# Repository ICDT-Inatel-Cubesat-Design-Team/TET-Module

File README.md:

<div align="center">
  
</div>
<h1 align="center">TET Module</h1>

<p align="center">

</p>

<p align="center">
    <a href="#overview">Overview</a> •
    <a href="#repository-organization">Repository Organization</a> •
    <a href="#releases">Releases</a> •
    <a href="#references">References</a> •
    <a href="#license">License</a>
</p>

## Overview
This project involves the development of the **TET (Telemetry, Encoding & Transmission)** module tailored for a 1U CubeSat platform. The system is engineered to handle TT&C (Tracking, Telemetry, and Command) capabilities, providing long-range telemetry and low-power wireless communication based on the Semtech LR1121 RF transceiver architecture and an STM32L431 microcontroller.

**Technical Parameters**
- **RF Architecture:** E80-900M2213S (LR1121)
- **Supported Bands:** Dual-band operation (915 MHz and 2.4 GHz)
- **Modulation Schemes:** LoRa, GFSK, FLRC, and LR-FHSS.
- **RF Interfaces:** Dedicated SMA/IPEX outputs for external antennas
- **External Interfaces:** SPI, GPIO, and CAN bus (via TCAN3414).
- **Power Input:** 3 independent 5 V input channels from the EPS (via PC/104)
- **Power Regulation:** Independent, regulated low-noise 3.3 V rail.
- **Onboard Sensors:** INA226 (current and voltage monitoring) and TMP112 (temperature monitoring and thermal alerts via I2C).
- **Storage:** 3 external SPI flash memories configured with TMR (Triple Modular Redundancy) for telemetry buffering and data storage.

## Repository Organization

* `docs`: Technical documentation and datasheets.
* `hardware`: Core hardware files.
    * `3D`: 3D models (.step).
    * `Fabrication`: BOM and Gerber files for JLCPCB manufacturing.
    * `PCB`: KiCad schematics and layout design.
* `firmware`: Examples of firmware implementation.

## Releases

<table>
  <thead>
    <tr>
      <th>Render</th>
      <th>Board Name</th>
      <th>Status</th>
      <th>Latest Release</th>
      <th>Date</th>
      <th>Datasheet</th>
      <th>BOM</th>
      <th>Ordering Info</th>
    </tr>
  </thead>
  <tbody>
    <tr>
      <td></td>
      <td>TET Module v1</td>
      <td>🧪 Testing</td>
      <td><a href="https://github.com/ICDT-Inatel-Cubesat-Design-Team/TET-Module/releases/tag/v1r2">v1r2</a></td>
      <td>09-06-2026</td>
      <td></td>
      <td>Yes</td>
      <td><a href="hardware/Fabrication/GERBER-TET.zip">GERBER</a> (JLCPCB)</td>
    </tr>
  </tbody>
</table>

## References

This project was inspired by the [TTC](https://github.com/spacelab-ufsc/ttc) and [TTC2](https://github.com/spacelab-ufsc/ttc2) modules from [SpaceLab](https://github.com/spacelab-ufsc/spacelab) UFSC, and the [Build a CubeSat](https://buildacubesat.space/) project. Thank you to both for making your work open-source, and a special thanks to the Build a CubeSat community for their support.

**Missions Associated with this Project**

<p>

<p>

## License

This project is licensed under the permissive, weakly-reciprocal **[CERN-OHL-W-2.0](LICENSE)** open-hardware license. You are free to modify and distribute these files, provided downstream hardware design modifications remain under the same terms.

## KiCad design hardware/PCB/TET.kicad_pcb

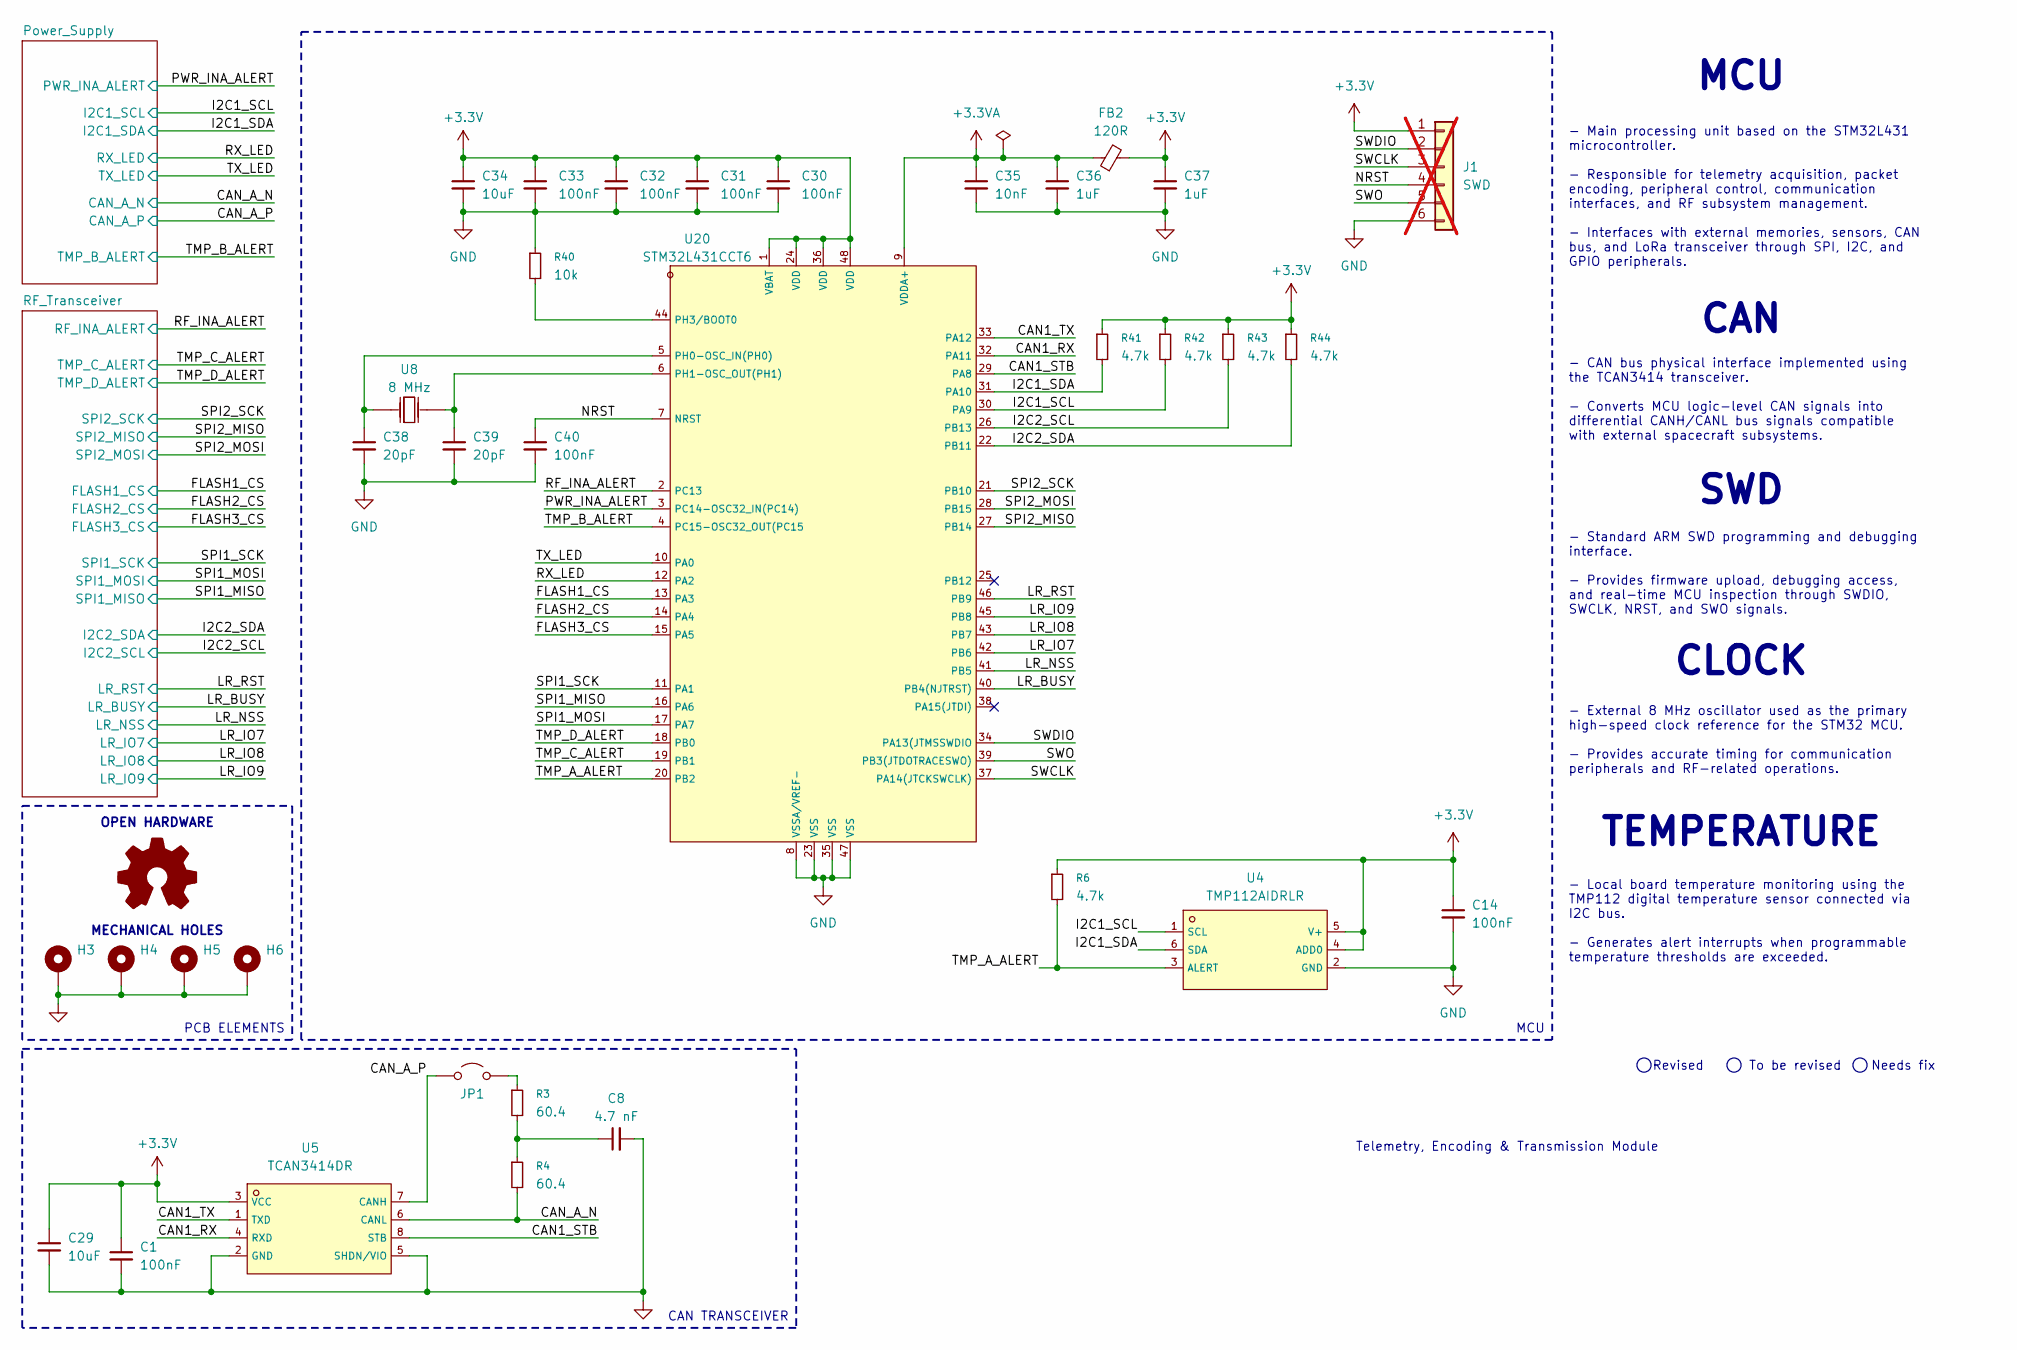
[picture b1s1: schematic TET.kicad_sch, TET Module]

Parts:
C1, C14, C30, C31, C32, C33, C40: 100nF; C_0402_1005Metric
C8: 4.7 nF; C_0402_1005Metric
C29, C34: 10uF; C_0805_2012Metric
C35: 10nF; C_0402_1005Metric
C36, C37: 1uF; C_0402_1005Metric
C38, C39: 20pF; C_0402_1005Metric
FB2: 120R; L_0603_1608Metric; LCSC C14709
H3, H4, H5, H6: MountingHole_Pad; MountingHole_3.2mm_M3_Pad_Via
J1: SWD; PinHeader_1x06_P2.54mm_Vertical; not fitted
JP1: Jumper_2_Open; SolderJumper-2_P1.3mm_Open_TrianglePad1.0x1.5mm
R3, R4: 60.4; R_0402_1005Metric
R6, R41, R42, R43, R44: 4.7k; R_0402_1005Metric
R40: 10k; R_0402_1005Metric
REF1: Logo_Open_Hardware_Small; OSHW-Logo_5.7x6mm_SilkScreen
U4: TMP112AIDRLR; SOT-563_L1.6-W1.2-P0.50-LS1.6-BR; LCSC C28927
U5: TCAN3414DR; SOIC-8_L4.9-W3.9-P1.27-LS6.0-BL; LCSC C22396693
U8: 8 MHz; CRYSTAL-SMD_L5.0-W3.2; LCSC C115962
U20: STM32L431CCT6; LQFP-48_L7.0-W7.0-P0.50-LS9.0-BL; LCSC C486681

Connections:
+3.3V: C1.1, C14.1, C29.1, C30.1, C31.1, C32.1, C33.1, C34.1, C37.1, FB2.2, J1.1, R6.1, R41.1, R42.1, R43.1, R44.1, U4.4 (ADD0), U4.5 (V+), U5.3 (VCC), U20.1 (VBAT), U20.24 (VDD), U20.36 (VDD), U20.48 (VDD); also elsewhere on the board
+3.3VA: C35.1, C36.1, FB2.1, U20.9 (VDDA+)
/CAN1_RX: U5.4 (RXD), U20.32 (PA11)
/CAN1_STB: U5.8 (STB), U20.29 (PA8)
/CAN1_TX: U5.1 (TXD), U20.33 (PA12)
/CAN_A_N: R4.2, U5.6 (CANL); also elsewhere on the board
/CAN_A_P: JP1.1 (A), U5.7 (CANH); also elsewhere on the board
/FLASH1_CS: U20.13 (PA3); also elsewhere on the board
/FLASH2_CS: U20.14 (PA4); also elsewhere on the board
/FLASH3_CS: U20.15 (PA5); also elsewhere on the board
/I2C1_SCL: R42.2, U4.1 (SCL), U20.30 (PA9); also elsewhere on the board
/I2C1_SDA: R41.2, U4.6 (SDA), U20.31 (PA10); also elsewhere on the board
/I2C2_SCL: R43.2, U20.26 (PB13); also elsewhere on the board
/I2C2_SDA: R44.2, U20.22 (PB11); also elsewhere on the board
/LR_BUSY: U20.40 (PB4(NJTRST)); also elsewhere on the board
/LR_IO7: U20.42 (PB6); also elsewhere on the board
/LR_IO8: U20.43 (PB7); also elsewhere on the board
/LR_IO9: U20.45 (PB8); also elsewhere on the board
/LR_NSS: U20.41 (PB5); also elsewhere on the board
/LR_RST: U20.46 (PB9); also elsewhere on the board
/NRST: C40.1, J1.4, U20.7 (NRST)
/PWR_INA_ALERT: U20.3 (PC14-OSC32_IN(PC14)); also elsewhere on the board
/RF_INA_ALERT: U20.2 (PC13); also elsewhere on the board
/RX_LED: U20.12 (PA2); also elsewhere on the board
/SPI1_MISO: U20.16 (PA6); also elsewhere on the board
/SPI1_MOSI: U20.17 (PA7); also elsewhere on the board
/SPI1_SCK: U20.11 (PA1); also elsewhere on the board
/SPI2_MISO: U20.27 (PB14); also elsewhere on the board
/SPI2_MOSI: U20.28 (PB15); also elsewhere on the board
/SPI2_SCK: U20.21 (PB10); also elsewhere on the board
/SWCLK: J1.3, U20.37 (PA14(JTCKSWCLK))
/SWDIO: J1.2, U20.34 (PA13(JTMSSWDIO)
/SWO: J1.5, U20.39 (PB3(JTDOTRACESWO))
/TMP_A_ALERT: R6.2, U4.3 (ALERT), U20.20 (PB2)
/TMP_B_ALERT: U20.4 (PC15-OSC32_OUT(PC15); also elsewhere on the board
/TMP_C_ALERT: U20.19 (PB1); also elsewhere on the board
/TMP_D_ALERT: U20.18 (PB0); also elsewhere on the board
/TX_LED: U20.10 (PA0); also elsewhere on the board
GND: C1.2, C8.2, C14.2, C29.2, C30.2, C31.2, C32.2, C33.2, C34.2, C35.2, C36.2, C37.2, C38.2, C39.2, C40.2, H3.1 (1_1), H4.1 (1_1), H5.1 (1_1), H6.1 (1_1), J1.6, R40.1, U4.2 (GND), U5.2 (GND), U5.5 (SHDN/VIO), U20.8 (VSSA/VREF-), U20.23 (VSS), U20.35 (VSS), U20.47 (VSS); also elsewhere on the board
unnamed: C8.1, R3.2, R4.1
unnamed: JP1.2 (B), R3.1
unnamed: C38.1, U8.2 (OSC2), U20.5 (PH0-OSC_IN(PH0))
unnamed: C39.1, U8.1 (OSC1), U20.6 (PH1-OSC_OUT(PH1))
unnamed: R40.2, U20.44 (PH3/BOOT0)

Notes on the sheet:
SWD
Revised
TEMPERATURE
Needs fix
MCU
OPEN HARDWARE
CLOCK
MECHANICAL HOLES
To be revised
CAN
Telemetry, Encoding & Transmission Module
PCB ELEMENTS
CAN TRANSCEIVER
- Main processing unit based on the STM32L431 microcontroller. - Responsible for telemetry acquisition, packet encoding, peripheral control, communication interfaces, and RF subsystem management. - Interfaces with external memories, sensors, CAN bus, and LoRa transceiver through SPI, I2C, and GPIO 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

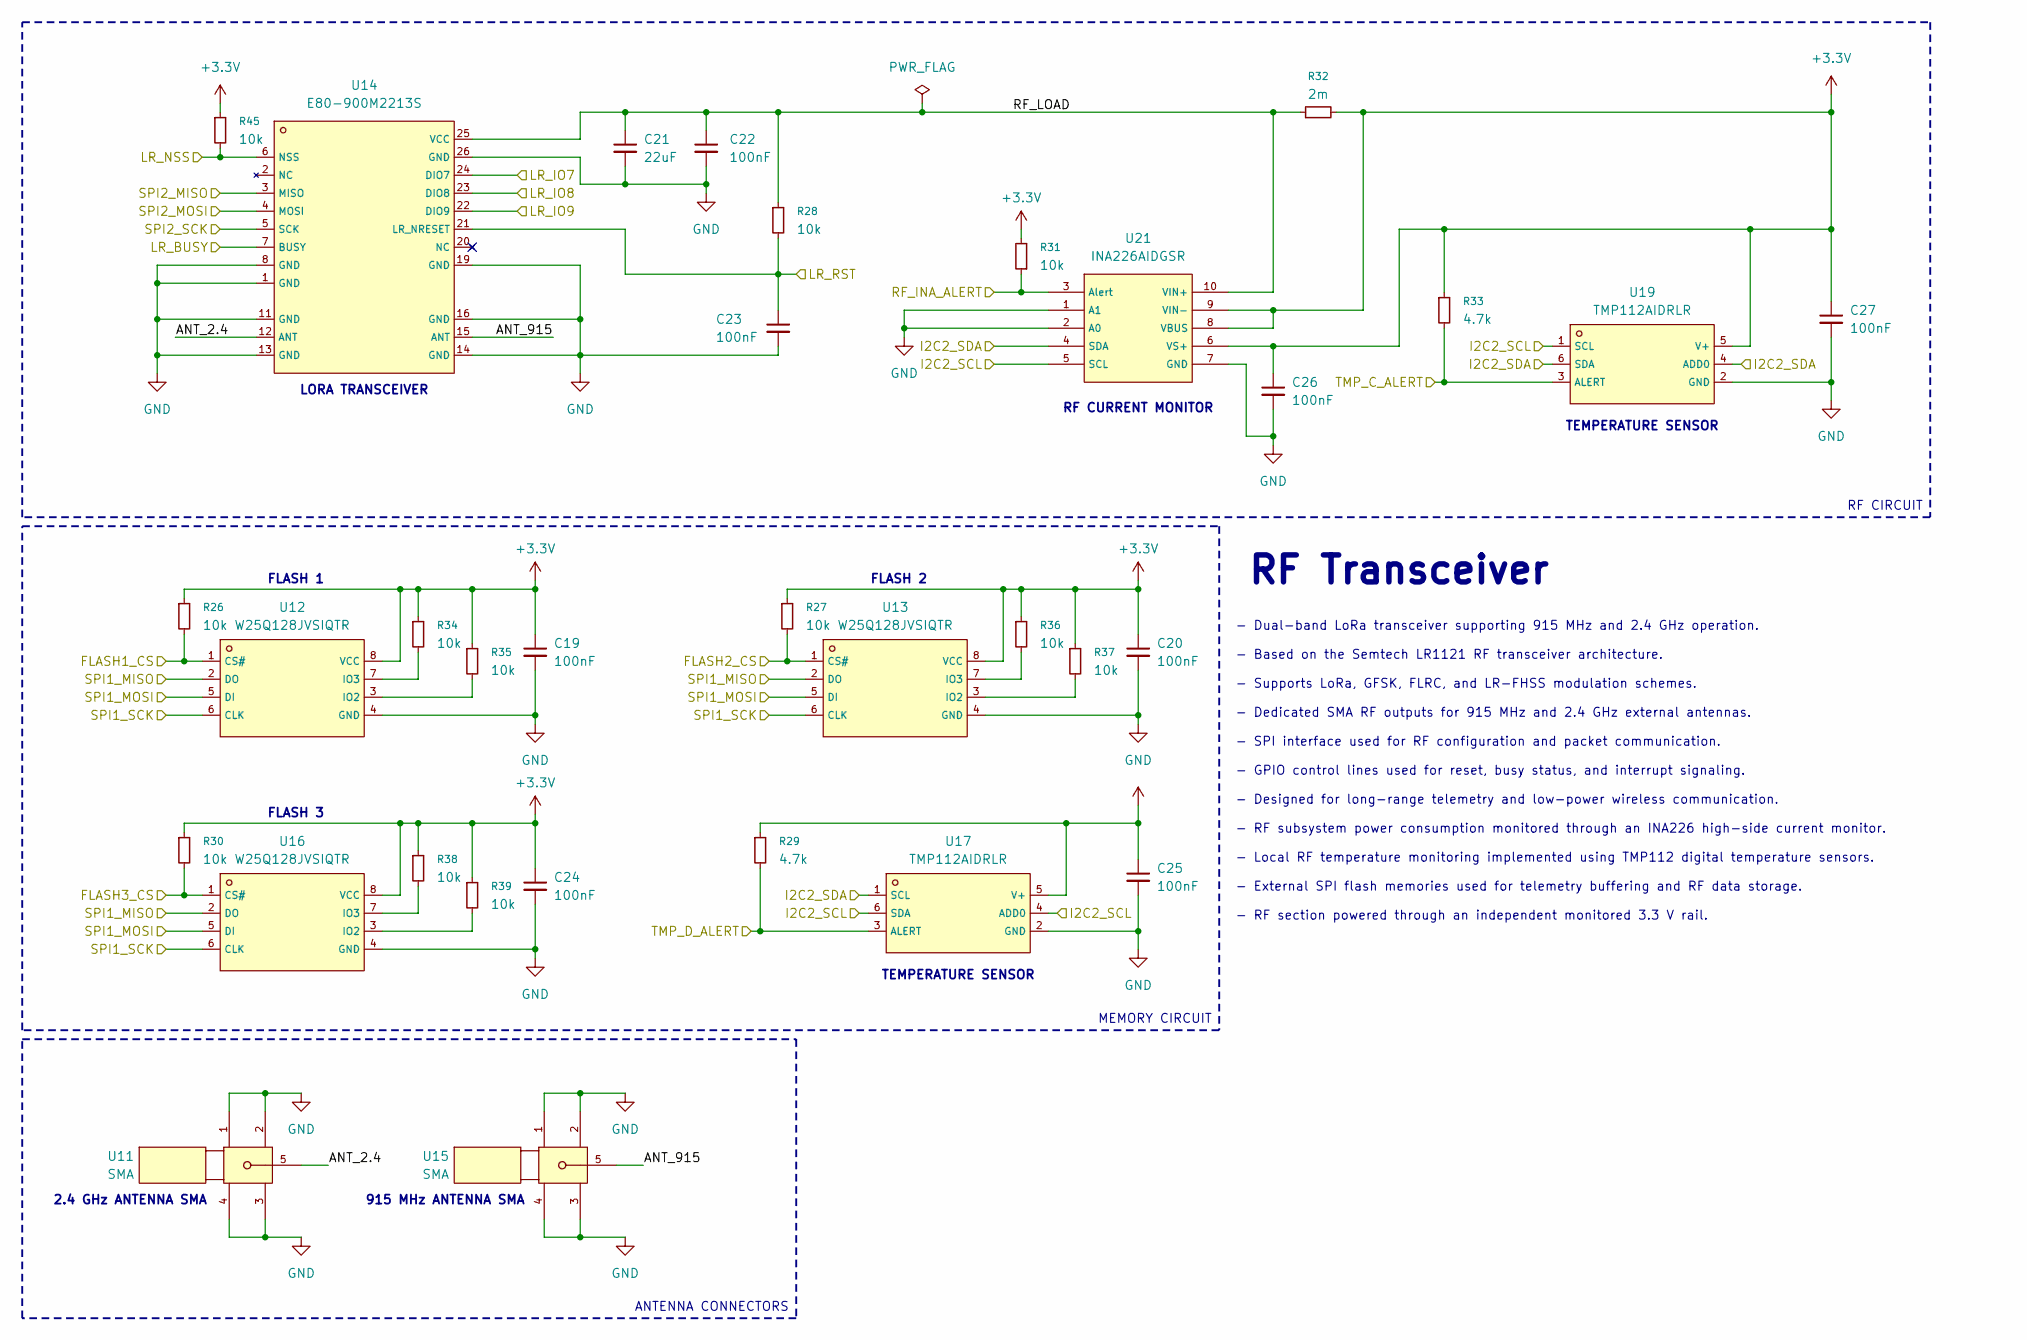
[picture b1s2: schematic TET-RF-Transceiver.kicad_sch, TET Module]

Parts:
C19, C20, C22, C23, C24, C25, C26, C27: 100nF; C_0402_1005Metric
C21: 22uF; C_0805_2012Metric
R26, R27, R28, R30, R31, R34, R35, R36, R37, R38, R39, R45: 10k; R_0402_1005Metric
R29, R33: 4.7k; R_0402_1005Metric
R32: 2m; RES-SMD_L6.3-W3.1-1; LCSC C695817
U11, U15: SMA; SMA-TH_SMA-KWE_C7498154; LCSC C7498154
U12, U13, U16: W25Q128JVSIQTR; SOIC-8_L5.3-W5.3-P1.27-LS8.0-BL; LCSC C97521
U14: E80-900M2213S; WIFIM-SMD_22P-L26.0-W16.0-P1.27-TL; LCSC C42464134
U17, U19: TMP112AIDRLR; SOT-563_L1.6-W1.2-P0.50-LS1.6-BR; LCSC C28927
U21: INA226AIDGSR; MSOP-10_L3.0-W3.0-P0.50-LS5.0-BL; LCSC C49851

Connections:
+3.3V: C19.1, C20.1, C24.1, C25.1, C26.1, C27.1, R26.1, R27.1, R29.1, R30.1, R31.2, R32.2, R33.1, R34.1, R35.1, R36.1, R37.1, R38.1, R39.1, R45.1, U12.8 (VCC), U13.8 (VCC), U16.8 (VCC), U17.5 (V+), U19.5 (V+), U21.6 (VS+), U21.8 (VBUS), U21.9 (VIN-); also elsewhere on the board
/FLASH1_CS: R26.2, U12.1 (CS#); also elsewhere on the board
/FLASH2_CS: R27.2, U13.1 (CS#); also elsewhere on the board
/FLASH3_CS: R30.2, U16.1 (CS#); also elsewhere on the board
/I2C2_SCL: U17.4 (ADD0), U17.6 (SDA), U19.1 (SCL), U21.5 (SCL); also elsewhere on the board
/I2C2_SDA: U17.1 (SCL), U19.4 (ADD0), U19.6 (SDA), U21.4 (SDA); also elsewhere on the board
/LR_BUSY: U14.7 (BUSY); also elsewhere on the board
/LR_IO7: U14.24 (DIO7); also elsewhere on the board
/LR_IO8: U14.23 (DIO8); also elsewhere on the board
/LR_IO9: U14.22 (DIO9); also elsewhere on the board
/LR_NSS: R45.2, U14.6 (NSS); also elsewhere on the board
/LR_RST: C23.1, R28.2, U14.21 (LR_NRESET); also elsewhere on the board
/RF_INA_ALERT: R31.1, U21.3 (Alert); also elsewhere on the board
/RF_Transceiver/ANT_2.4: U11.5, U14.12 (ANT)
/RF_Transceiver/ANT_915: U14.15 (ANT), U15.5
/RF_Transceiver/RF_LOAD: C21.1, C22.1, R28.1, R32.1, U14.25 (VCC), U21.10 (VIN+)
/SPI1_MISO: U12.2 (DO), U13.2 (DO), U16.2 (DO); also elsewhere on the board
/SPI1_MOSI: U12.5 (DI), U13.5 (DI), U16.5 (DI); also elsewhere on the board
/SPI1_SCK: U12.6 (CLK), U13.6 (CLK), U16.6 (CLK); also elsewhere on the board
/SPI2_MISO: U14.3 (MISO); also elsewhere on the board
/SPI2_MOSI: U14.4 (MOSI); also elsewhere on the board
/SPI2_SCK: U14.5 (SCK); also elsewhere on the board
/TMP_C_ALERT: R33.2, U19.3 (ALERT); also elsewhere on the board
/TMP_D_ALERT: R29.2, U17.3 (ALERT); also elsewhere on the board
GND: C19.2, C20.2, C21.2, C22.2, C23.2, C24.2, C25.2, C26.2, C27.2, U11.1, U11.2, U11.3, U11.4, U12.4 (GND), U13.4 (GND), U14.1 (GND), U14.8 (GND), U14.11 (GND), U14.13 (GND), U14.14 (GND), U14.16 (GND), U14.19 (GND), U14.26 (GND), U15.1, U15.2, U15.3, U15.4, U16.4 (GND), U17.2 (GND), U19.2 (GND), U21.1 (A1), U21.2 (A0), U21.7 (GND); also elsewhere on the board
unnamed: R35.2, U12.3 (IO2)
unnamed: R34.2, U12.7 (IO3)
unnamed: R37.2, U13.3 (IO2)
unnamed: R36.2, U13.7 (IO3)
unnamed: R39.2, U16.3 (IO2)
unnamed: R38.2, U16.7 (IO3)

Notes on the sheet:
TEMPERATURE SENSOR
915 MHz ANTENNA SMA
2.4 GHz ANTENNA SMA
FLASH 1
LORA TRANSCEIVER
RF CURRENT MONITOR
FLASH 3
FLASH 2
RF Transceiver
MEMORY CIRCUIT
- Dual-band LoRa transceiver supporting 915 MHz and 2.4 GHz operation. - Based on the Semtech LR1121 RF transceiver architecture. - Supports LoRa, GFSK, FLRC, and LR-FHSS modulation schemes. - Dedicated SMA RF outputs for 915 MHz and 2.4 GHz external antennas. - SPI interface used for RF configurat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
ANTENNA CONNECTORS
RF CIRCUIT

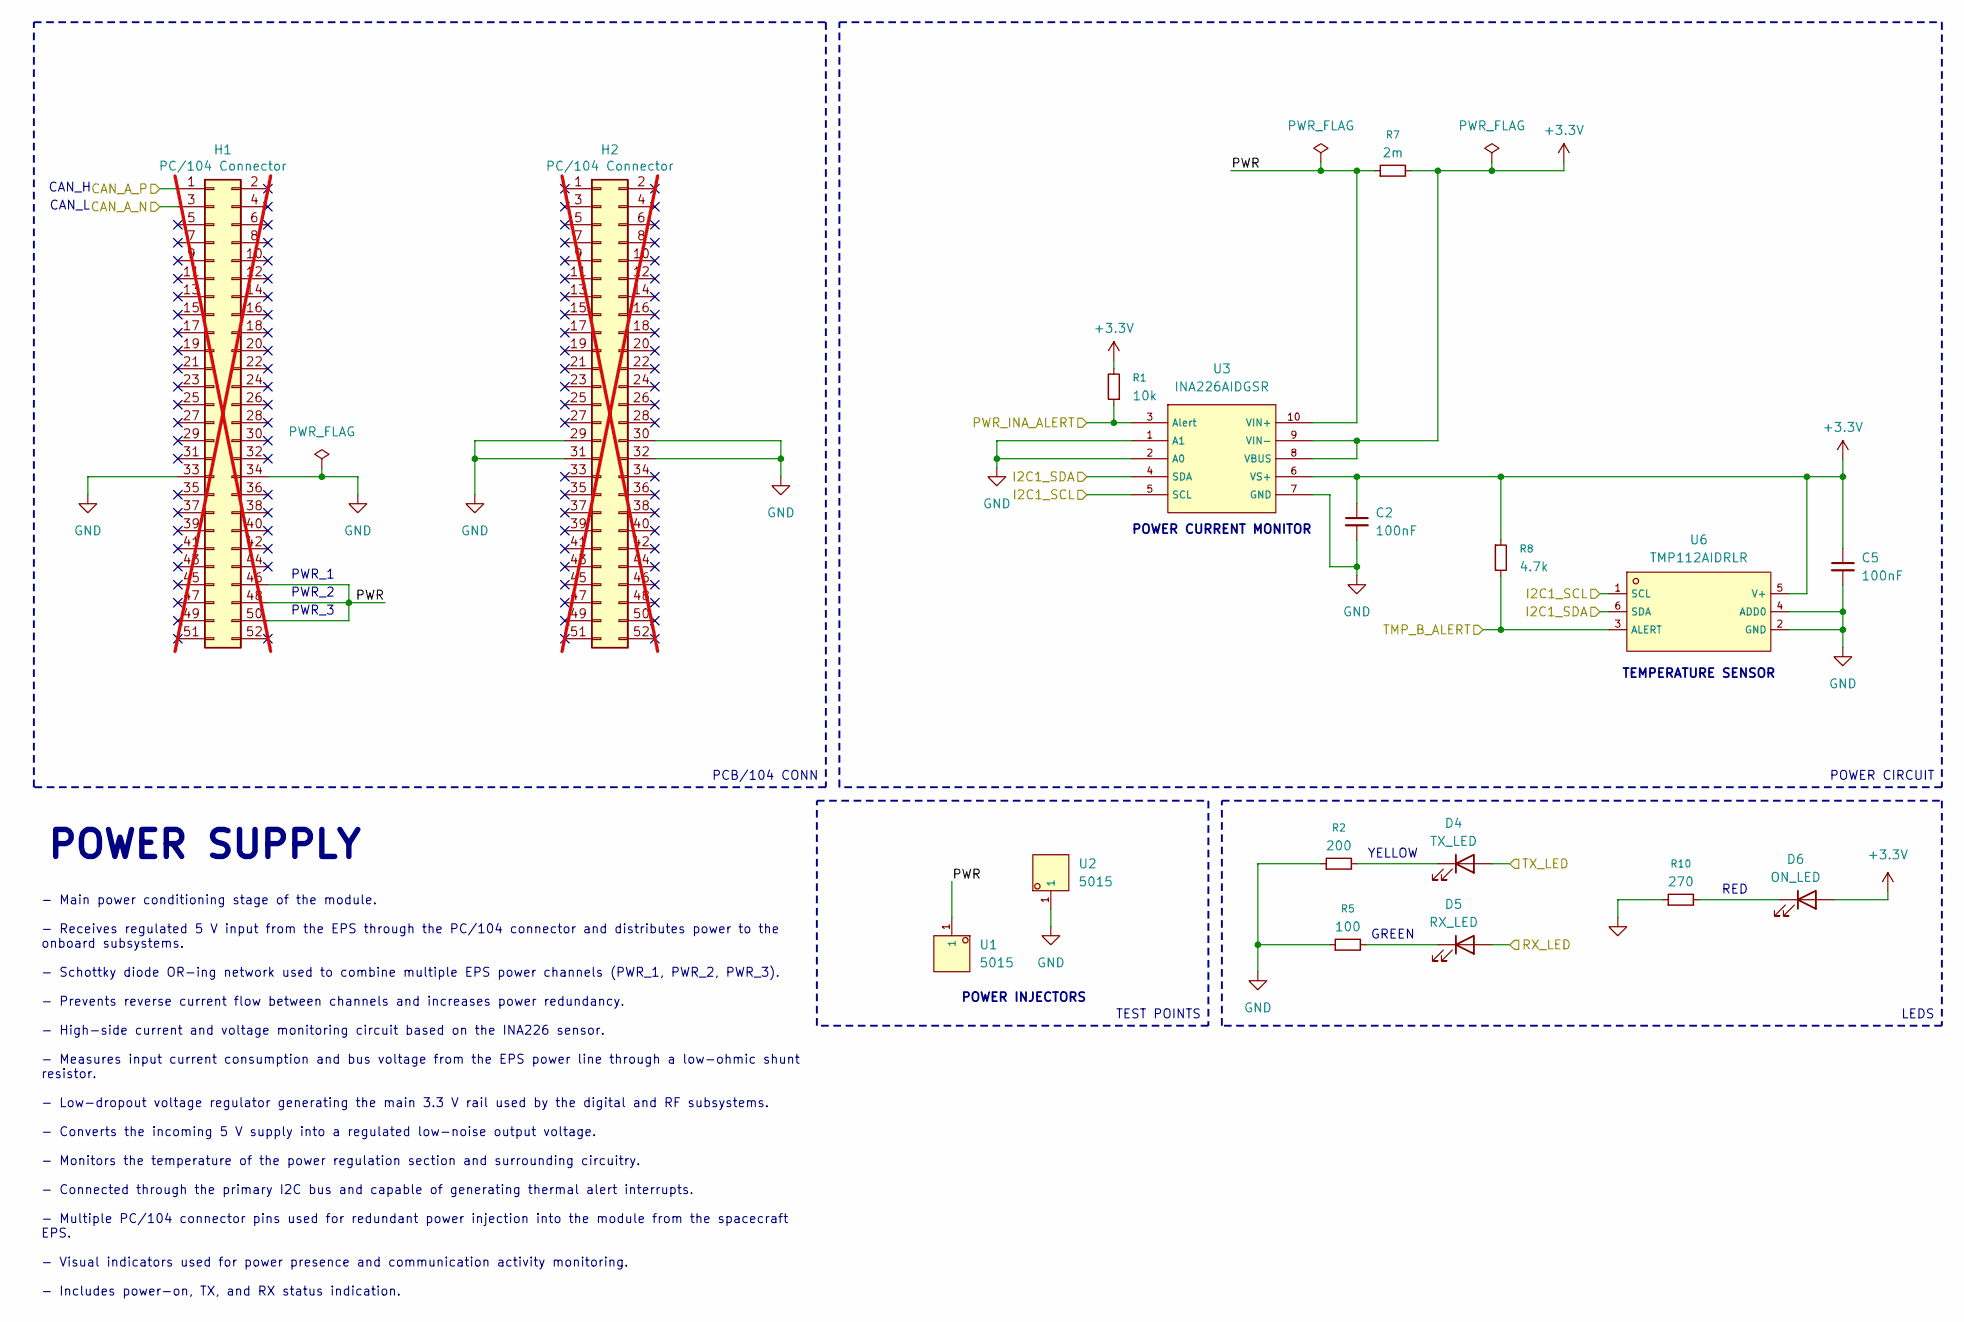
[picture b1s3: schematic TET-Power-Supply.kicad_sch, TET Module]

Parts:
C2, C5: 100nF; C_0402_1005Metric
D4: TX_LED; LED_0805_2012Metric; LCSC C2296
D5: RX_LED; LED_0805_2012Metric; LCSC C2297
D6: ON_LED; LED_0805_2012Metric; LCSC C84256
H1, H2: PC/104 Connector; PinHeader_2x26_P2.54mm_Vertical; not fitted
R1: 10k; R_0402_1005Metric
R2: 200; R_0402_1005Metric
R5: 100; R_0402_1005Metric
R7: 2m; RES-SMD_L6.3-W3.1-1; LCSC C695817
R8: 4.7k; R_0402_1005Metric
R10: 270; R_0402_1005Metric
U1, U2: 5015; TEST-SMD_L2.7-W1.0; LCSC C2906768
U3: INA226AIDGSR; MSOP-10_L3.0-W3.0-P0.50-LS5.0-BL; LCSC C49851
U6: TMP112AIDRLR; SOT-563_L1.6-W1.2-P0.50-LS1.6-BR; LCSC C28927

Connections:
+3.3V: C2.1, C5.1, D6.2 (A), R1.2, R7.2, R8.1, U3.6 (VS+), U3.8 (VBUS), U3.9 (VIN-), U6.5 (V+); also elsewhere on the board
/CAN_A_N: H1.3; also elsewhere on the board
/CAN_A_P: H1.1; also elsewhere on the board
/I2C1_SCL: U3.5 (SCL), U6.1 (SCL); also elsewhere on the board
/I2C1_SDA: U3.4 (SDA), U6.6 (SDA); also elsewhere on the board
/PWR_INA_ALERT: R1.1, U3.3 (Alert); also elsewhere on the board
/Power_Supply/PWR: H1.46, H1.48, H1.50, R7.1, U1.1 (1_1), U3.10 (VIN+)
/RX_LED: D5.2 (A); also elsewhere on the board
/TMP_B_ALERT: R8.2, U6.3 (ALERT); also elsewhere on the board
/TX_LED: D4.2 (A); also elsewhere on the board
GND: C2.2, C5.2, H1.33, H1.34, H2.29, H2.30, H2.31, H2.32, R2.1, R5.1, R10.1, U2.1 (1_1), U3.1 (A1), U3.2 (A0), U3.7 (GND), U6.2 (GND), U6.4 (ADD0); also elsewhere on the board
unnamed: D4.1 (K), R2.2
unnamed: D5.1 (K), R5.2
unnamed: D6.1 (K), R10.2

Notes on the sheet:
POWER INJECTORS
CAN_L
POWER SUPPLY
TEMPERATURE SENSOR
POWER CURRENT MONITOR
CAN_H
RED
PWR_2
YELLOW
PWR_1
PWR_3
GREEN
TEST POINTS
PCB/104 CONN
- Main power conditioning stage of the module. - Receives regulated 5 V input from the EPS through the PC/104 connector and distributes power to the onboard subsystems. - Schottky diode OR-ing network used to combine multiple EPS power channels (PWR_1, PWR_2, PWR_3). - Prevents reverse current flow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
POWER CIRCUIT
LEDS

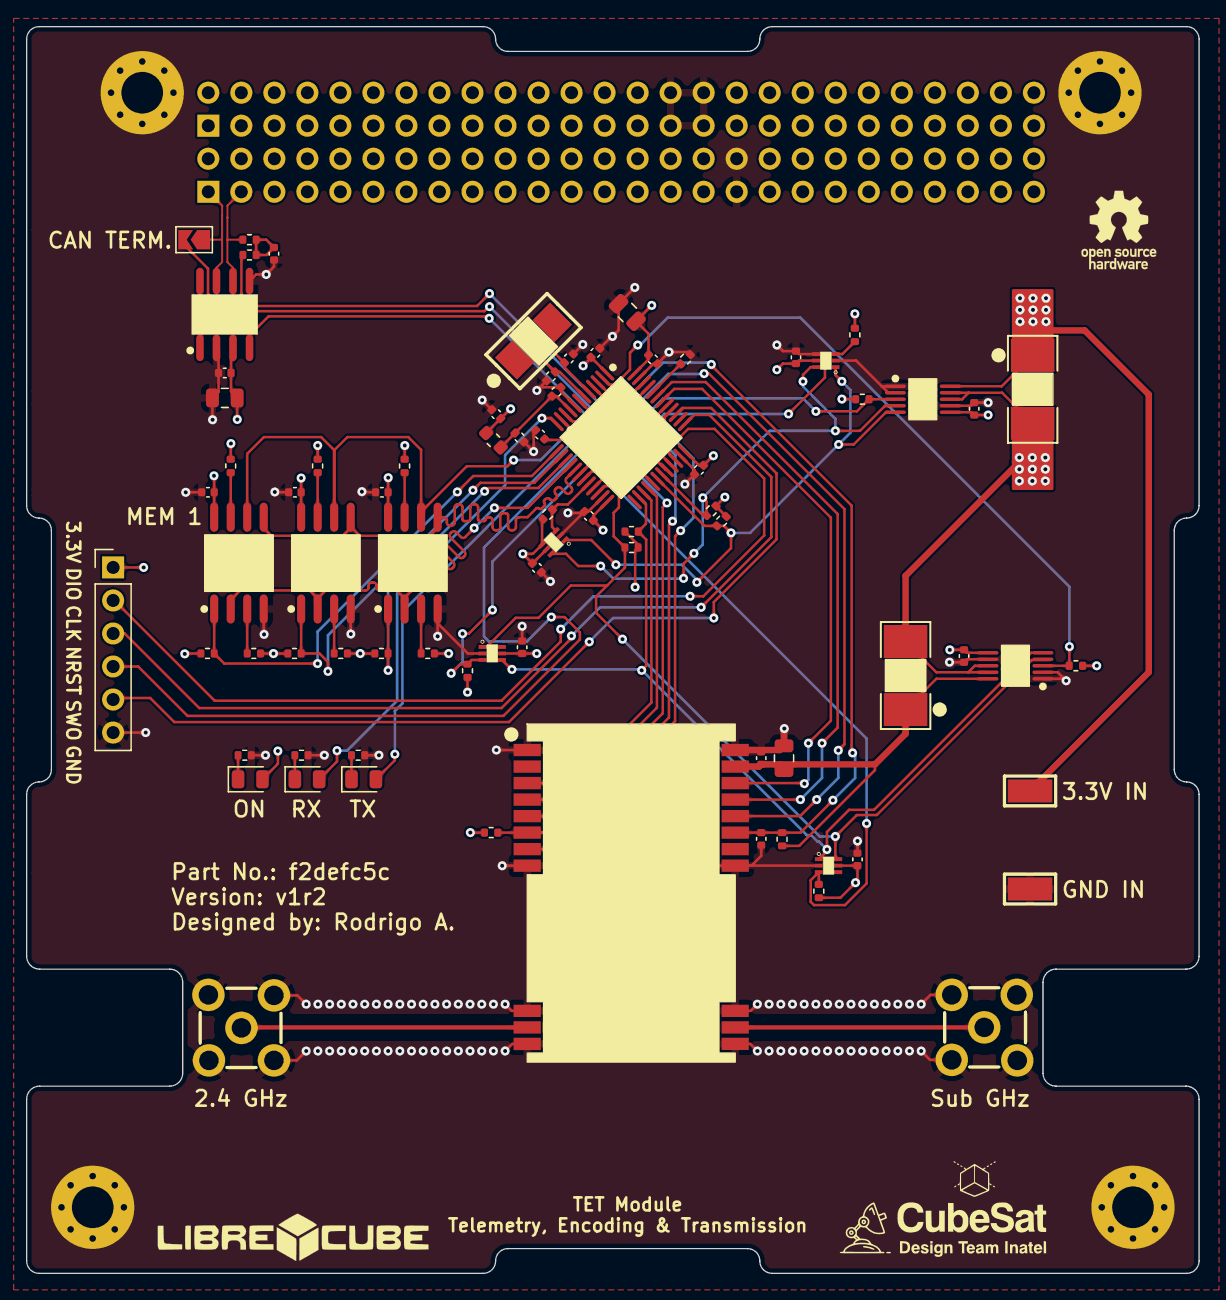
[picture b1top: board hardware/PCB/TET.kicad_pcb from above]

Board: 4 copper layers, 90.2 x 95.9 mm, 85 parts (0 on the bottom side), 57 nets.

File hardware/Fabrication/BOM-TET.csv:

Comment,Designator,Footprint,LCSC,Quantity
100,R5,R_0402_1005Metric,C25076,1
100nF,"C1,C14,C19,C2,C20,C22,C23,C24,C25,C26,C27,C30,C31,C32,C33,C40,C5",C_0402_1005Metric,C307331,17
10k,"R1,R26,R27,R28,R30,R31,R34,R35,R36,R37,R38,R39,R40,R45",R_0402_1005Metric,C25744,14
10nF,C35,C_0402_1005Metric,C15195,1
10uF,"C29,C34",C_0805_2012Metric,C440198,2
120R,FB2,L_0603_1608Metric,C14709,1
1uF,"C36,C37",C_0402_1005Metric,C52923,2
200,R2,R_0402_1005Metric,C25087,1
20pF,"C38,C39",C_0402_1005Metric,C1554,2
22uF,C21,C_0805_2012Metric,C45783,1
270,R10,R_0402_1005Metric,C2909342,1
2m,"R32,R7",RES-SMD_L6.3-W3.1-1,C695817,2
4.7 nF,C8,C_0402_1005Metric,C1538,1
4.7k,"R29,R33,R41,R42,R43,R44,R6,R8",R_0402_1005Metric,C25900,8
5015,"U1,U2",TEST-SMD_L2.7-W1.0,C2906768,2
60.4,"R3,R4",R_0402_1005Metric,C137954,2
8 MHz,U8,CRYSTAL-SMD_L5.0-W3.2,C115962,1
E80-900M2213S,U14,WIFIM-SMD_22P-L26.0-W16.0-P1.27-TL,C42464134,1
INA226AIDGSR,"U21,U3",MSOP-10_L3.0-W3.0-P0.50-LS5.0-BL,C49851,2
ON_LED,D6,LED_0805_2012Metric,C84256,1
RX_LED,D5,LED_0805_2012Metric,C2297,1
SMA,"U11,U15",SMA-TH_SMA-KWE_C7498154,C7498154,2
STM32L431CCT6,U20,LQFP-48_L7.0-W7.0-P0.50-LS9.0-BL,C486681,1
TCAN3414DR,U5,SOIC-8_L4.9-W3.9-P1.27-LS6.0-BL,C22396693,1
TMP112AIDRLR,"U17,U19,U4,U6",SOT-563_L1.6-W1.2-P0.50-LS1.6-BR,C28927,4
TX_LED,D4,LED_0805_2012Metric,C2296,1
W25Q128JVSIQTR,"U12,U13,U16",SOIC-8_L5.3-W5.3-P1.27-LS8.0-BL,C97521,3

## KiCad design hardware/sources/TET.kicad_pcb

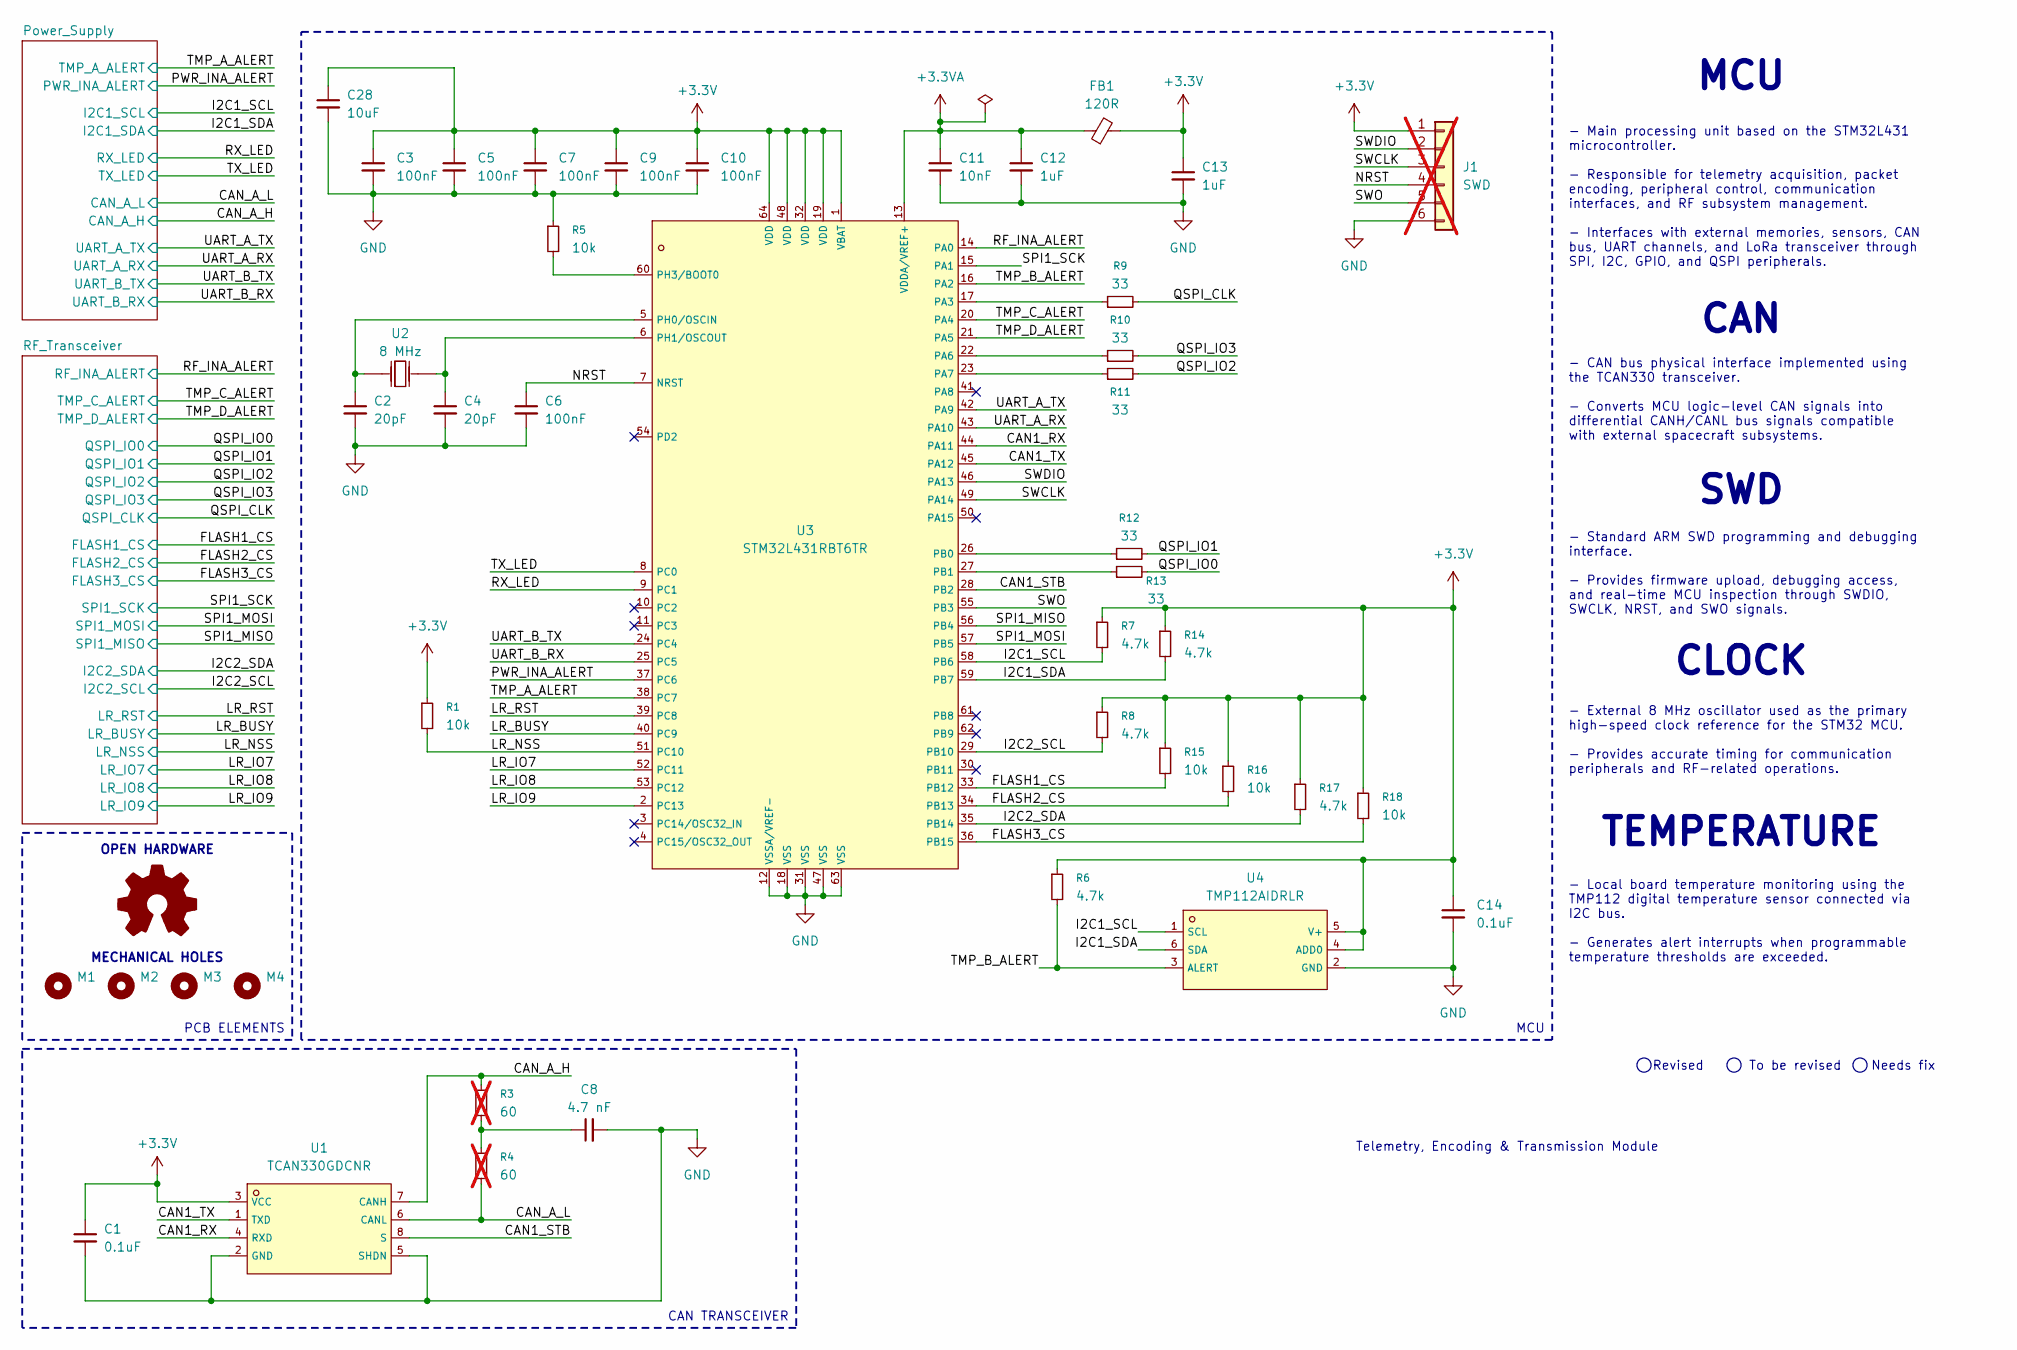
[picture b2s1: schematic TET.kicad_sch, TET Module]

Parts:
C1, C14: 0.1uF; C_0603_1608Metric
C2, C4: 20pF; C_0603_1608Metric
C3, C5, C6, C7, C9, C10: 100nF; C_0603_1608Metric
C8: 4.7 nF; C_0603_1608Metric
C11: 10nF; C_0603_1608Metric
C12, C13: 1uF; C_0603_1608Metric
C28: 10uF; C_0603_1608Metric
FB1: 120R; L_0603_1608Metric; LCSC C14709
J1: SWD; PinHeader_1x06_P2.54mm_Vertical; not fitted
M1, M2, M3, M4: MountingHole; MountingHole_3.2mm_M3_Pad
R1, R5, R15, R16, R18: 10k; R_0603_1608Metric
R3, R4: 60; R_0603_1608Metric_Pad0.98x0.95mm_HandSolder; not fitted
R6, R7, R8, R14, R17: 4.7k; R_0603_1608Metric
R9, R10, R11, R12, R13: 33; R_0603_1608Metric
REF1: Logo_Open_Hardware_Small; OSHW-Logo_5.7x6mm_SilkScreen
U1: TCAN330GDCNR; SOT-23-8_L2.9-W1.6-P0.65-LS2.8-BL; LCSC C191006
U2: 8 MHz; CRYSTAL-SMD_L5.0-W3.2; LCSC C115962
U3: STM32L431RBT6TR; LQFP-64_L10.0-W10.0-P0.50-LS12.0-BL; LCSC C2053549
U4: TMP112AIDRLR; SOT-563_L1.6-W1.2-P0.50-LS1.6-BR; LCSC C28927

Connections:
+3.3V: C1.1, C3.1, C5.1, C7.1, C9.1, C10.1, C13.1, C14.1, C28.1, FB1.2, J1.1, R1.1, R6.1, R7.1, R8.1, R14.1, R15.1, R16.1, R17.1, R18.1, U1.3 (VCC), U3.1 (VBAT), U3.19 (VDD), U3.32 (VDD), U3.48 (VDD), U3.64 (VDD), U4.4 (ADD0), U4.5 (V+); also elsewhere on the board
+3.3VA: C11.1, C12.1, FB1.1, U3.13 (VDDA/VREF+)
/CAN1_RX: U1.4 (RXD), U3.44 (PA11)
/CAN1_STB: U1.8 (S), U3.28 (PB2)
/CAN1_TX: U1.1 (TXD), U3.45 (PA12)
/CAN_A_H: R3.1, U1.7 (CANH); also elsewhere on the board
/CAN_A_L: R4.2, U1.6 (CANL); also elsewhere on the board
/FLASH1_CS: R15.2, U3.33 (PB12); also elsewhere on the board
/FLASH2_CS: R16.2, U3.34 (PB13); also elsewhere on the board
/FLASH3_CS: R18.2, U3.36 (PB15); also elsewhere on the board
/I2C1_SCL: R7.2, U3.58 (PB6), U4.1 (SCL); also elsewhere on the board
/I2C1_SDA: R14.2, U3.59 (PB7), U4.6 (SDA); also elsewhere on the board
/I2C2_SCL: R8.2, U3.29 (PB10); also elsewhere on the board
/I2C2_SDA: R17.2, U3.35 (PB14); also elsewhere on the board
/LR_BUSY: U3.40 (PC9); also elsewhere on the board
/LR_IO7: U3.52 (PC11); also elsewhere on the board
/LR_IO8: U3.53 (PC12); also elsewhere on the board
/LR_IO9: U3.2 (PC13); also elsewhere on the board
/LR_NSS: R1.2, U3.51 (PC10); also elsewhere on the board
/LR_RST: U3.39 (PC8); also elsewhere on the board
/NRST: C6.1, J1.4, U3.7 (NRST)
/PWR_INA_ALERT: U3.37 (PC6); also elsewhere on the board
/QSPI_CLK: R9.2; also elsewhere on the board
/QSPI_IO0: R13.2; also elsewhere on the board
/QSPI_IO1: R12.2; also elsewhere on the board
/QSPI_IO2: R11.2; also elsewhere on the board
/QSPI_IO3: R10.2; also elsewhere on the board
/RF_INA_ALERT: U3.14 (PA0); also elsewhere on the board
/RX_LED: U3.9 (PC1); also elsewhere on the board
/SPI1_MISO: U3.56 (PB4); also elsewhere on the board
/SPI1_MOSI: U3.57 (PB5); also elsewhere on the board
/SPI1_SCK: U3.15 (PA1); also elsewhere on the board
/SWCLK: J1.3, U3.49 (PA14)
/SWDIO: J1.2, U3.46 (PA13)
/SWO: J1.5, U3.55 (PB3)
/TMP_A_ALERT: U3.38 (PC7); also elsewhere on the board
/TMP_B_ALERT: R6.2, U3.16 (PA2), U4.3 (ALERT)
/TMP_C_ALERT: U3.20 (PA4); also elsewhere on the board
/TMP_D_ALERT: U3.21 (PA5); also elsewhere on the board
/TX_LED: U3.8 (PC0); also elsewhere on the board
/UART_A_RX: U3.43 (PA10); also elsewhere on the board
/UART_A_TX: U3.42 (PA9); also elsewhere on the board
/UART_B_RX: U3.25 (PC5); also elsewhere on the board
/UART_B_TX: U3.24 (PC4); also elsewhere on the board
GND: C1.2, C2.2, C3.2, C4.2, C5.2, C6.2, C7.2, C8.2, C9.2, C10.2, C11.2, C12.2, C13.2, C14.2, C28.2, J1.6, R5.1, U1.2 (GND), U1.5 (SHDN), U3.12 (VSSA/VREF-), U3.18 (VSS), U3.31 (VSS), U3.47 (VSS), U3.63 (VSS), U4.2 (GND); also elsewhere on the board
unnamed: C8.1, R3.2, R4.1
unnamed: C4.1, U2.1 (OSC1), U3.6 (PH1/OSCOUT)
unnamed: C2.1, U2.2 (OSC2), U3.5 (PH0/OSCIN)
unnamed: R9.1, U3.17 (PA3)
unnamed: R10.1, U3.22 (PA6)
unnamed: R11.1, U3.23 (PA7)
unnamed: R12.1, U3.26 (PB0)
unnamed: R13.1, U3.27 (PB1)
unnamed: R5.2, U3.60 (PH3/BOOT0)

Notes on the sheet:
SWD
Revised
TEMPERATURE
Needs fix
MCU
OPEN HARDWARE
CLOCK
MECHANICAL HOLES
To be revised
CAN
Telemetry, Encoding & Transmission Module
PCB ELEMENTS
CAN TRANSCEIVER
- Main processing unit based on the STM32L431 microcontroller. - Responsible for telemetry acquisition, packet encoding, peripheral control, communication interfaces, and RF subsystem management. - Interfaces with external memories, sensors, CAN bus, UART channels, and LoRa transceiver through SPI,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
